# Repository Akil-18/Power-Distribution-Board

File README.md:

# Power-Distribution-Board

**INTRODUCTION**

The power distribution board PCB, designed using KiCad for Technocrats Robotics, efficiently manages and distributes three distinct voltage levels - 5V, 12V, and 24V. The board features an optimized PCB layout that provides a compact design, maximizing space utilization within the Rover’s enclosure. This ensures that all critical components of the Rover receive the appropriate power supply for optimal operation.

**SCHEMATIC DIAGRAM**

**PCB LAYOUT**

**3D VIEW**

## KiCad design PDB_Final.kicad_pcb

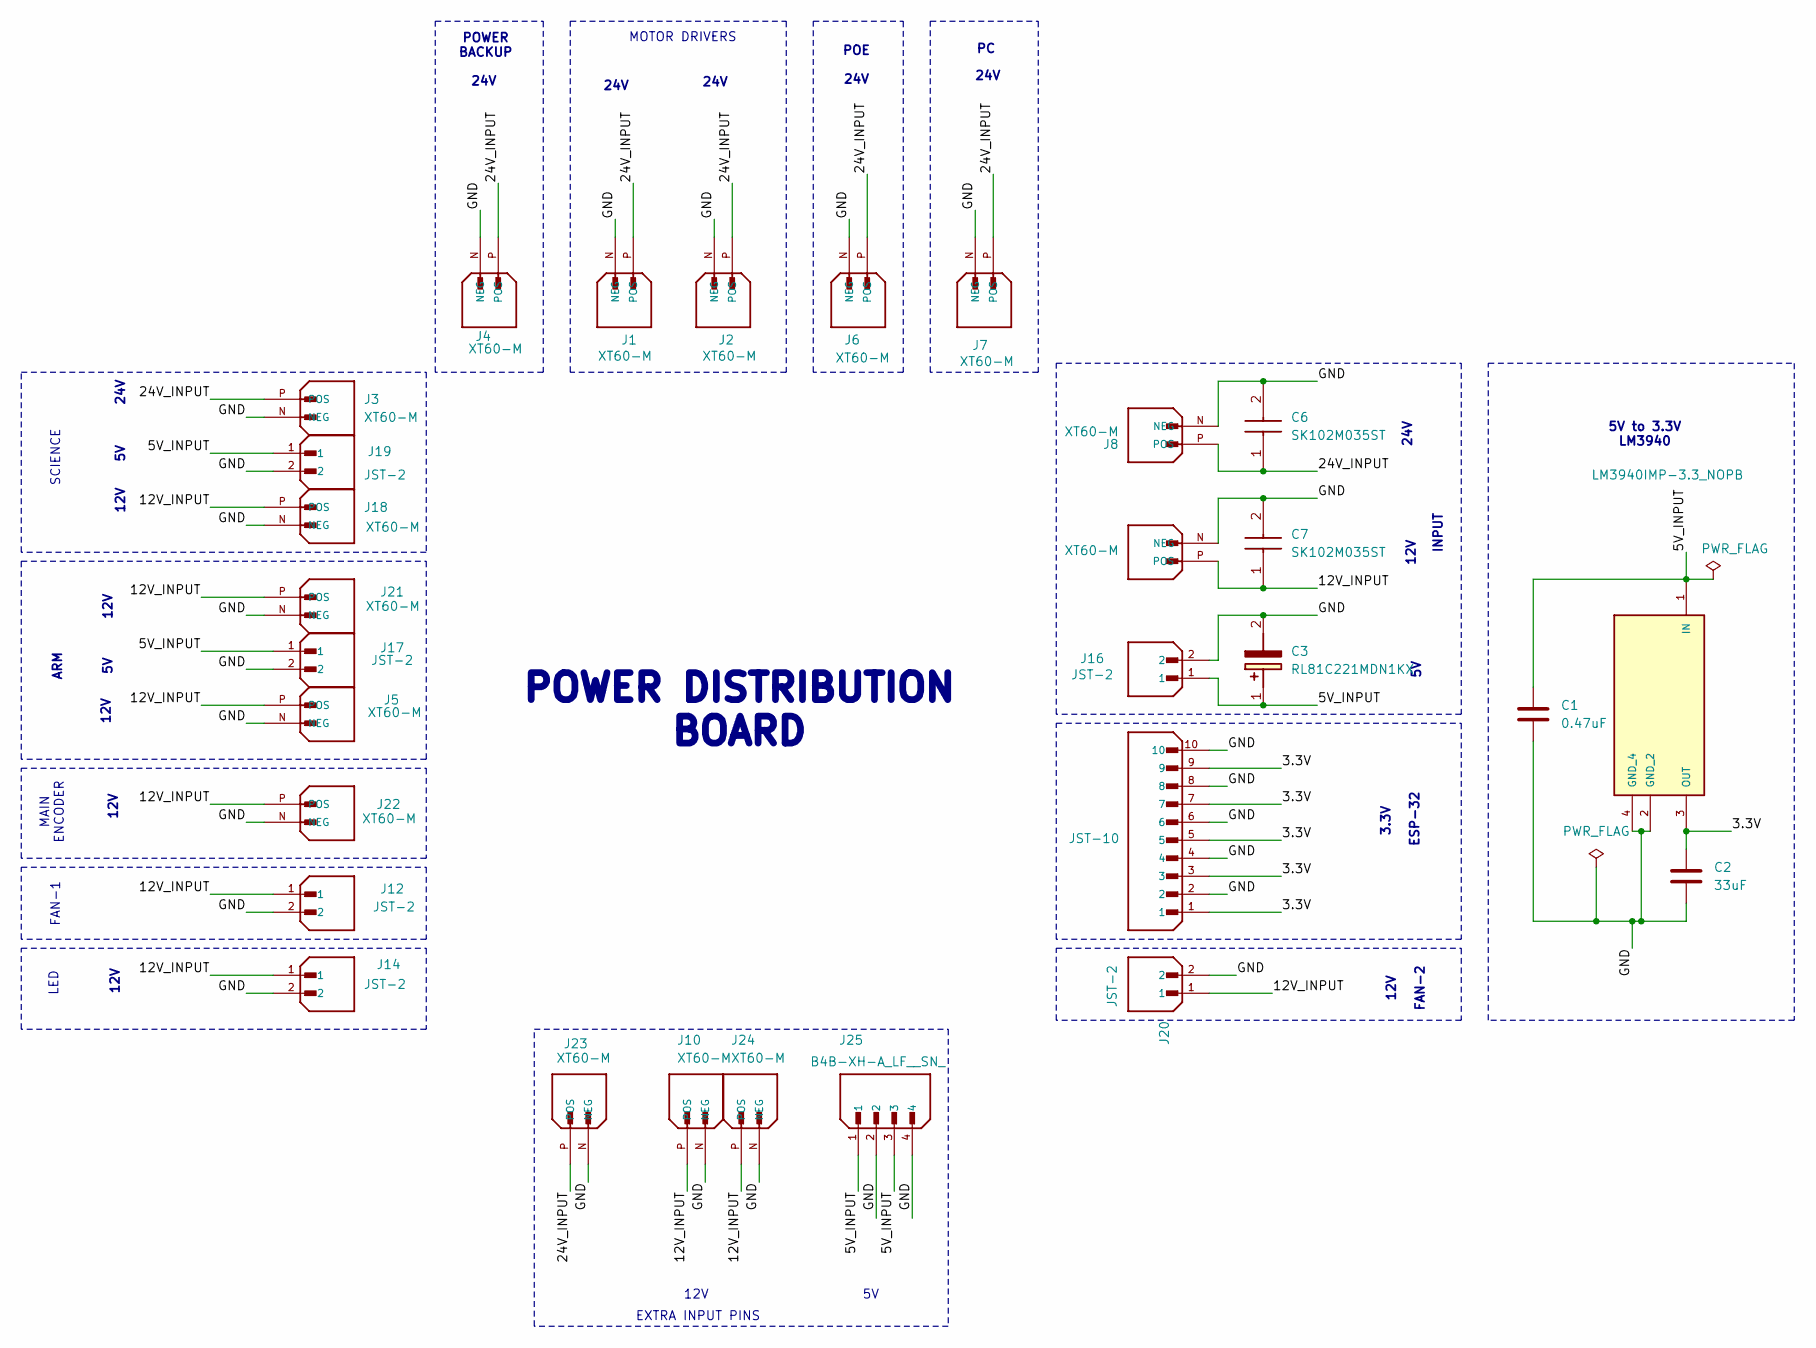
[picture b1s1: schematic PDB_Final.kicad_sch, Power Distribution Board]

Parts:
C1: 0.47uF; C0805
C2: 33uF; CAPC1608X80N
C3: RL81C221MDN1KX; CAPPRD350W60D800H900; Manufacturer_Part_Number RL81C221MDN1KX; Mouser Part Number 647-RL81C221MDN1KX
C6, C7: SK102M035ST; CAPPRD500W65D1300H2100; Manufacturer_Part_Number SK102M035ST; Mouser Part Number 598-SK102M035ST
J1, J2, J3, J4, J5, J6, J7, J8, J9, J10, J18, J21, J22, J23, J24: XT60-M; AMASS_XT60-M; PARTREV V1.2
J12, J14, J16, J17, J19, J20: JST-2; JST_XH_B2B-XH-A_1x02_P2.50mm_Vertical; PARTREV N/A
J15: JST-10; JST_XH_B10B-XH-A_1x10_P2.50mm_Vertical; PARTREV 7/4/21
J25: B4B-XH-A_LF__SN_; JST_XH_B4B-XH-A_1x04_P2.50mm_Vertical; PARTREV 7/4/21
VR1: LM3940IMP-3.3_NOPB; VREG_LM3940IMP-3.3_NOPB; PARTREV G

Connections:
/3.3V: C2.1, J15.1, J15.3, J15.5, J15.7, J15.9, VR1.3 (OUT)
/5V_INPUT: C1.1, C3.1 (+), J16.1, J17.1, J19.1, J25.1, J25.3, VR1.1 (IN)
/12V_INPUT: C7.1 (+), J5.P (POS), J9.P (POS), J10.P (POS), J12.1, J14.1, J18.P (POS), J20.1, J21.P (POS), J22.P (POS), J24.P (POS)
/24V_INPUT: C6.1 (+), J1.P (POS), J2.P (POS), J3.P (POS), J4.P (POS), J6.P (POS), J7.P (POS), J8.P (POS), J23.P (POS)
/GND: C1.2, C2.2, C3.2 (-), C6.2 (-), C7.2 (-), J1.N (NEG), J2.N (NEG), J3.N (NEG), J4.N (NEG), J5.N (NEG), J6.N (NEG), J7.N (NEG), J8.N (NEG), J9.N (NEG), J10.N (NEG), J12.2, J14.2, J15.2, J15.4, J15.6, J15.8, J15.10, J16.2, J17.2, J18.N (NEG), J19.2, J20.2, J21.N (NEG), J22.N (NEG), J23.N (NEG), J24.N (NEG), J25.2, J25.4, VR1.2 (GND_2), VR1.4 (GND_4)

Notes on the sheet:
12V
24V
ARM
5V to 3.3V LM3940
FAN-1
12V
MAIN ENCODER
FAN-2
POE
3.3V
24V
MOTOR DRIVERS
EXTRA INPUT PINS
INPUT
POWER DISTRIBUTION BOARD
ESP-32
LED
POWER BACKUP
SCIENCE

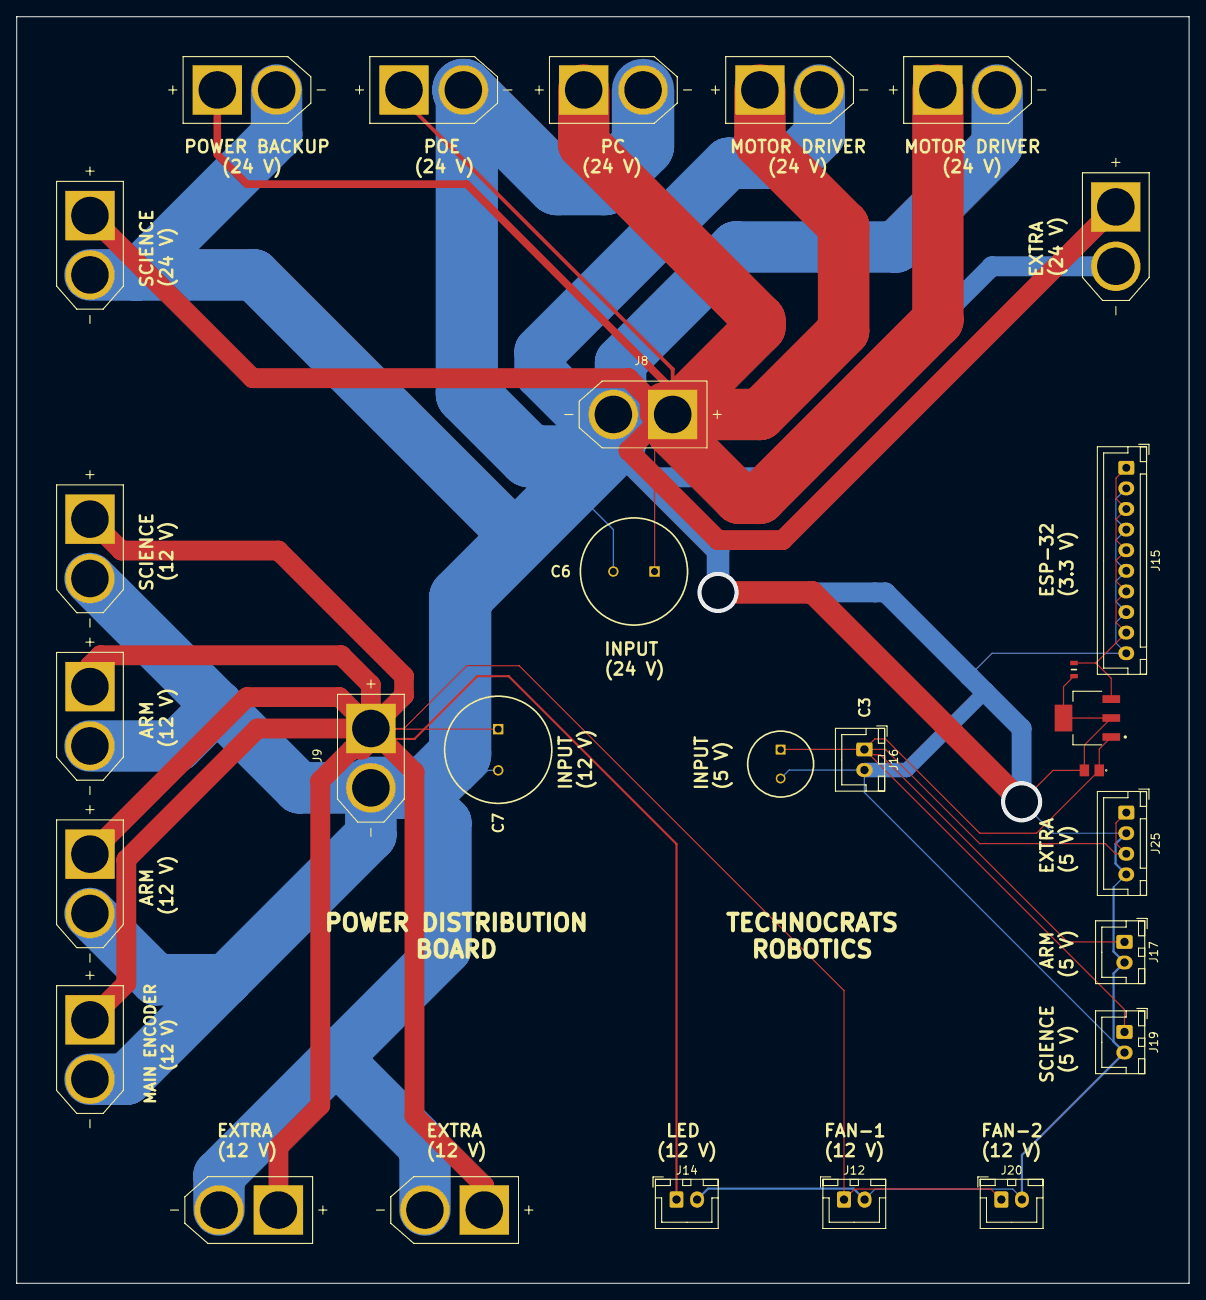
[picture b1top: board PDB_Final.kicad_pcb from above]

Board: 2 copper layers, 142.2 x 153.7 mm, 29 parts (0 on the bottom side), 5 nets.

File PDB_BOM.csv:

"Reference","Value","Datasheet","Footprint","Qty","DNP"
"C1","0.47uF","~","470nf_KiCad:C0805","1",""
"C2","33uF","~","33uf_KiCad:CAPC1608X80N","1",""
"C3","RL81C221MDN1KX","http://nichicon-us.com/english/products/pdfs/e-rl8.pdf","16V - 220 µF KiCad:CAPPRD350W60D800H900","1",""
"C6,C7","SK102M035ST","https://componentsearchengine.com/Datasheets/2/SK102M035ST.pdf","35V (1000uf) or 50V (470uf) KiCad:CAPPRD500W65D1300H2100","2",""
"J1,J2,J3,J4,J5,J6,J7,J8,J9,J10,J11,J18,J21,J22,J23,J24","XT60-M","","XT60-Male:AMASS_XT60-M","16",""
"J12,J14,J16,J17,J19,J20","JST-2","","Connector_JST:JST_XH_B2B-XH-A_1x02_P2.50mm_Vertical","6",""
"J15","JST-10","","Connector_JST:JST_XH_B10B-XH-A_1x10_P2.50mm_Vertical","1",""
"J25","B4B-XH-A_LF__SN_","","Connector_JST:JST_XH_B4B-XH-A_1x04_P2.50mm_Vertical","1",""
"VR1","LM3940IMP-3.3_NOPB","","LM3940IMP-3.3_NOPB (1):VREG_LM3940IMP-3.3_NOPB","1",""

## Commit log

2024-08-05 README.md
